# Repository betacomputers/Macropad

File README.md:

# Macropad
My first time working on a hardware electronics project. Still learning PCB design. The current design for this macropad has 9 keys, a rotary encoder, an OLED display and is backlit with 4 LEDs, running on QMK firmware.

## Features
* 2 Part case: top printed in white PLA, bottom printed in clear HT filament
* 9 Keys
* EC11 Rotary encoder
* 2 WS2812B RGB LEDs
* 128x32 OLED Display

## Cad Model
Made in Fusion360.
PCB is mounted to the bottom of the case with 4 M3 bolts and 5x4mm heat inserts. Top and bottom of the case are connected with snap fit joints.

## PCB
Made in KiCad.
My first attempt at making a PCB, no idea how it'll turn out. All DRC errors appear to be related to KiCads default clearance settings for the LEDs being too large.

Schematic:

Footprint:

3D View (top, bottom):

## BOM
* 10x 1N4148 Diodes
* 9x MX-Style switches
* 9x DSA keycaps
* 4x SK6812 MINI-E LEDs
* 4x M3 screws
* 4x M3x5mx4mm heatset inserts
* 1x EC11 Rotary encoder
* 1x 0.91 inch OLED display
* 1x Seeed XIAO RP2040

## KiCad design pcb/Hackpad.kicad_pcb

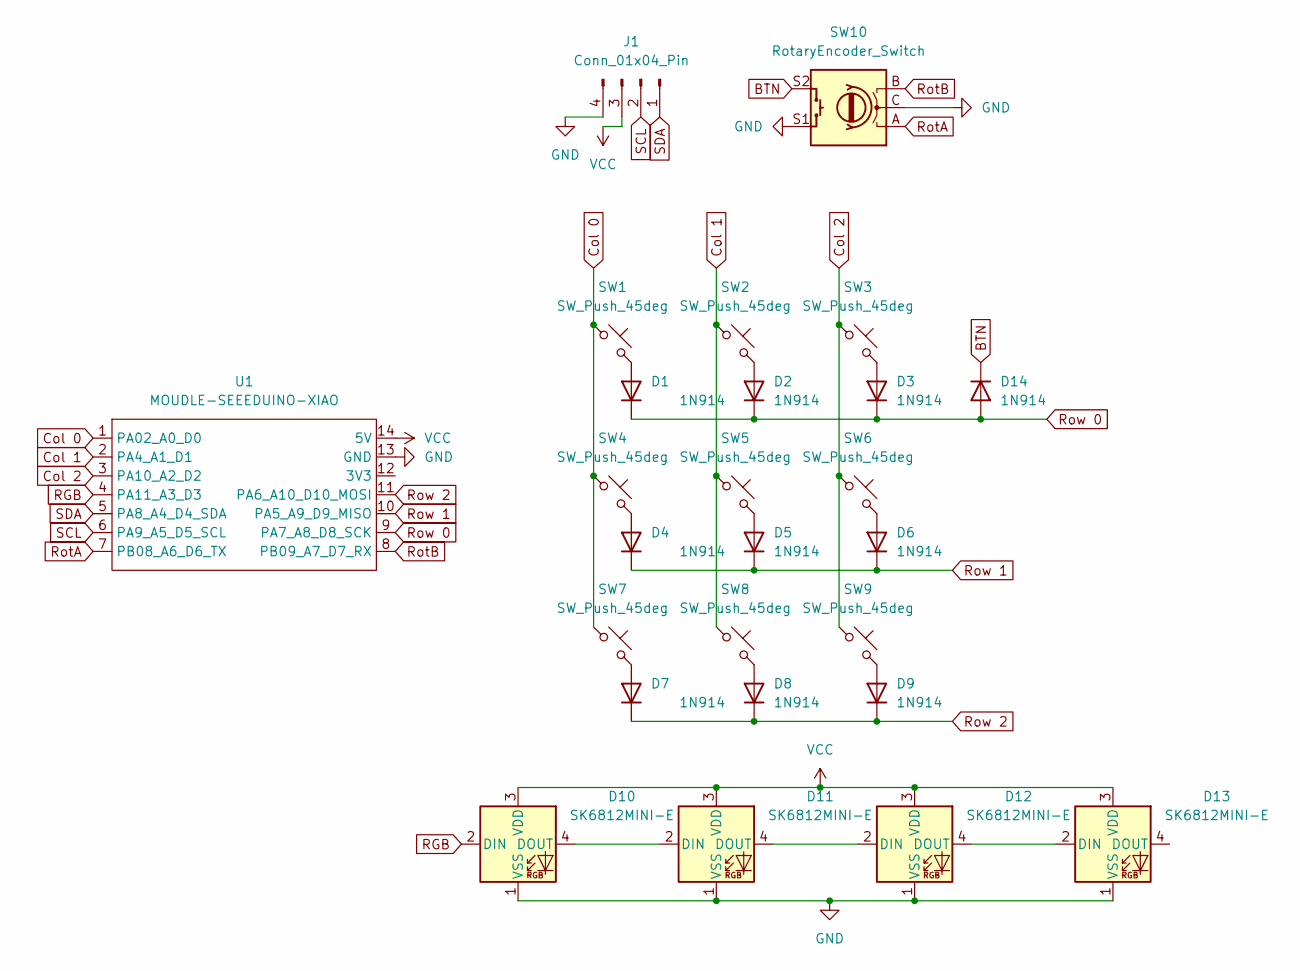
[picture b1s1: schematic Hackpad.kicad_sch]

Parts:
D1, D2, D3, D4, D5, D6, D7, D8, D9, D14: 1N914; D_DO-35_SOD27_P7.62mm_Horizontal
D10, D11, D12, D13: SK6812MINI-E; LED_SK6812MINI-E_3.2x2.8mm_P1.5mm_ReverseMount
J1: Conn_01x04_Pin; PinHeader_1x04_P2.54mm_Vertical
SW1, SW2, SW3, SW4, SW5, SW6, SW7, SW8, SW9: SW_Push_45deg; SW_Cherry_MX_1.00u_PCB
SW10: RotaryEncoder_Switch; RotaryEncoder_Alps_EC11E-Switch_Vertical_H20mm
U1: MOUDLE-SEEEDUINO-XIAO; XIAO-Generic-Hybrid-14P-2.54-21X17.8MM

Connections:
BTN: D14.1 (K), SW10.S2
Col 0: SW1.1, SW4.1, SW7.1, U1.1 (PA02_A0_D0)
Col 1: SW2.1, SW5.1, SW8.1, U1.2 (PA4_A1_D1)
Col 2: SW3.1, SW6.1, SW9.1, U1.3 (PA10_A2_D2)
GND: D10.1 (VSS), D11.1 (VSS), D12.1 (VSS), D13.1 (VSS), J1.4, SW10.C, SW10.S1, U1.13 (GND)
unnamed: D1.2 (A), SW1.2
unnamed: D2.2 (A), SW2.2
unnamed: D3.2 (A), SW3.2
unnamed: D4.2 (A), SW4.2
unnamed: D5.2 (A), SW5.2
unnamed: D6.2 (A), SW6.2
unnamed: D7.2 (A), SW7.2
unnamed: D8.2 (A), SW8.2
unnamed: D9.2 (A), SW9.2
unnamed: D10.4 (DOUT), D11.2 (DIN)
unnamed: D11.4 (DOUT), D12.2 (DIN)
unnamed: D12.4 (DOUT), D13.2 (DIN)
RGB: D10.2 (DIN), U1.4 (PA11_A3_D3)
RotA: SW10.A, U1.7 (PB08_A6_D6_TX)
RotB: SW10.B, U1.8 (PB09_A7_D7_RX)
Row 0: D1.1 (K), D2.1 (K), D3.1 (K), D14.2 (A), U1.9 (PA7_A8_D8_SCK)
Row 1: D4.1 (K), D5.1 (K), D6.1 (K), U1.10 (PA5_A9_D9_MISO)
Row 2: D7.1 (K), D8.1 (K), D9.1 (K), U1.11 (PA6_A10_D10_MOSI)
SCL: J1.2, U1.6 (PA9_A5_D5_SCL)
SDA: J1.1, U1.5 (PA8_A4_D4_SDA)
VCC: D10.3 (VDD), D11.3 (VDD), D12.3 (VDD), D13.3 (VDD), J1.3, U1.14 (5V)

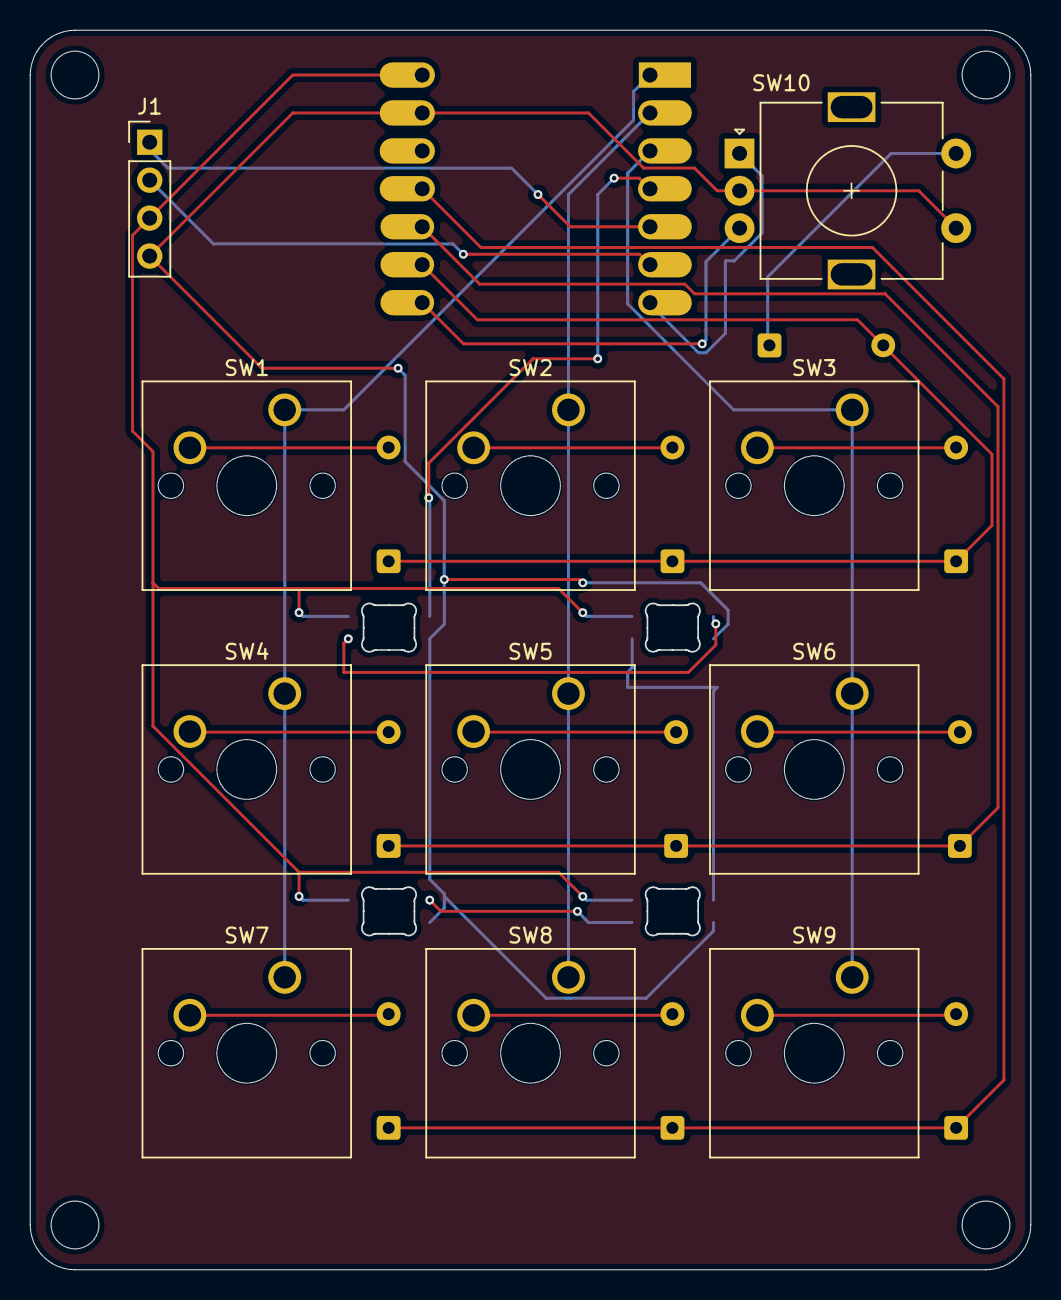
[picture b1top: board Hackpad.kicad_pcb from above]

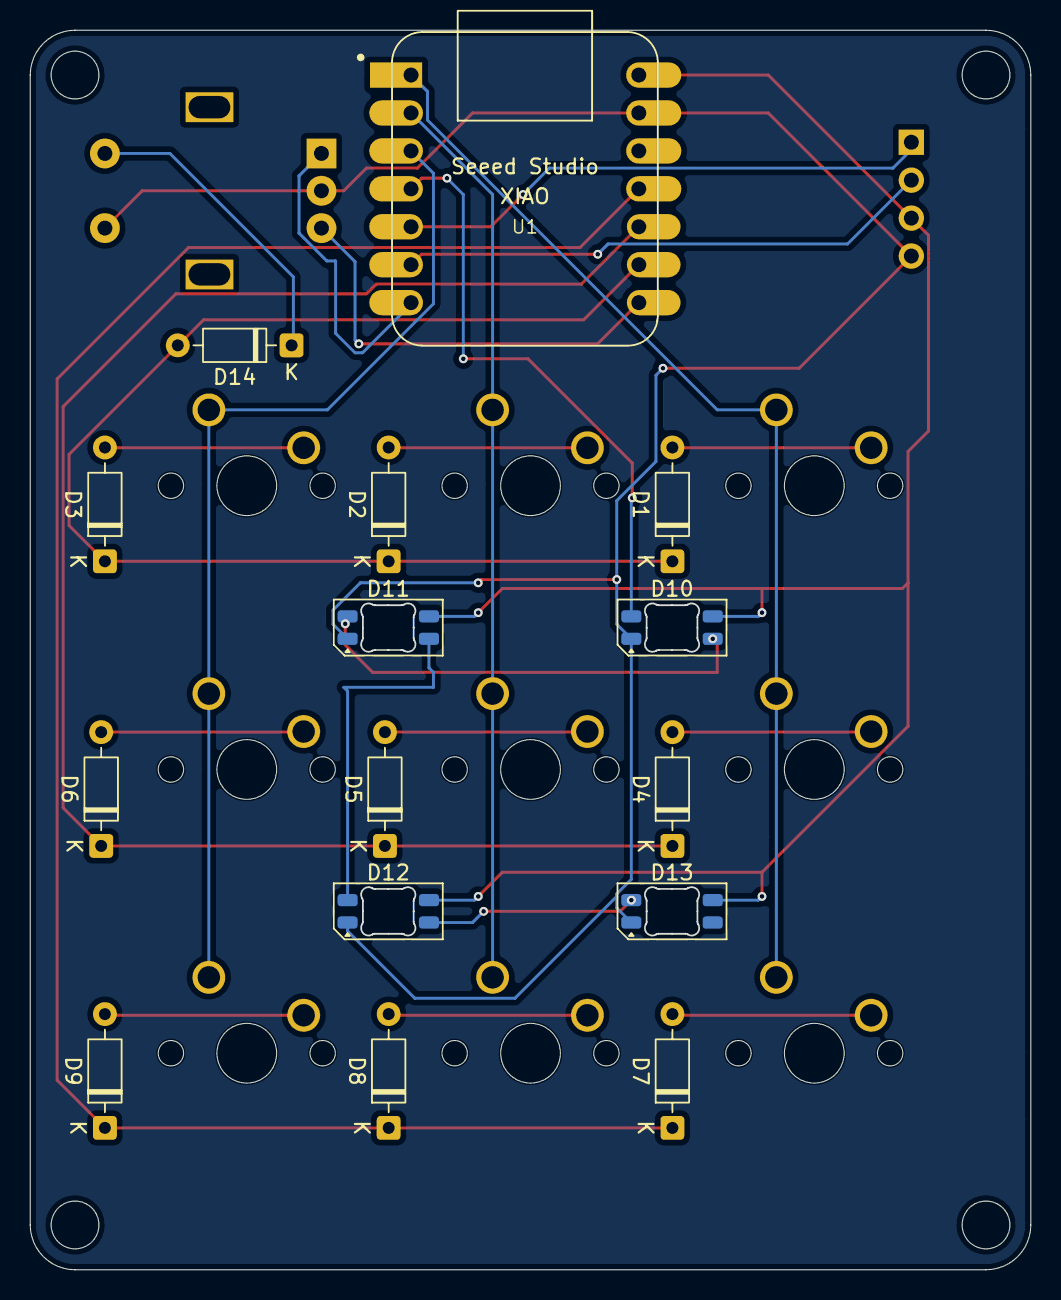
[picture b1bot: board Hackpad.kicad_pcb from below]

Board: 2 copper layers, 67.0 x 83.0 mm, 26 parts (15 on the bottom side), 26 nets.

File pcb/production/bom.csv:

Designator,Footprint,Quantity,Value,LCSC Part #
"D1, D14, D2, D3, D4, D5, D6, D7, D8, D9",D_DO-35_SOD27_P7.62mm_Horizontal,10,1N914,
"D10, D11, D12, D13",LED_SK6812MINI-E_3.2x2.8mm_P1.5mm_ReverseMount,4,SK6812MINI-E,
J1,PinHeader_1x04_P2.54mm_Vertical,1,Conn_01x04_Pin,
"SW1, SW2, SW3, SW4, SW5, SW6, SW7, SW8, SW9",SW_Cherry_MX_1.00u_PCB,9,SW_Push_45deg,
SW10,RotaryEncoder_Alps_EC11E-Switch_Vertical_H20mm,1,RotaryEncoder_Switch,
U1,XIAO-Generic-Hybrid-14P-2.54-21X17.8MM,1,MOUDLE-SEEEDUINO-XIAO,
